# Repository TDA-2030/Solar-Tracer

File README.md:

# 太阳追踪器

## 参考

- https://www.pveducation.org/zh-hans/pvcdrom/%E9%98%B3%E5%85%89%E7%9A%84%E5%B1%9E%E6%80%A7/%E5%A4%AA%E9%98%B3%E7%9A%84%E9%AB%98%E7%B2%BE%E5%BA%A6%E5%AE%9A%E4%BD%8D
- http://106.37.81.211:8082/images/sjsimages/pdf/xw/xwB215_hebing/Y2177876.pdf
- https://jonacappelle.github.io/Master-Thesis/_madgwick_a_h_r_s_8c.html
- https://gml.noaa.gov/grad/solcalc/
- https://zh.planetcalc.com/318/

## 编译

esp-idf 版本：8497af9b77

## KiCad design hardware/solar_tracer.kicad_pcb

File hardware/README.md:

# Ferris Wheel

```
 ________                          __                 __       __ __                         __ 
|        \                        |  \               |  \  _  |  |  \                       |  \
| $$$$$$$______   ______   ______  \$$ _______       | $$ / \ | $| $$____   ______   ______ | $$
| $$__  /      \ /      \ /      \|  \/       \      | $$/  $\| $| $$    \ /      \ /      \| $$
| $$  \|  $$$$$$|  $$$$$$|  $$$$$$| $|  $$$$$$$      | $$  $$$\ $| $$$$$$$|  $$$$$$|  $$$$$$| $$
| $$$$$| $$    $| $$   \$| $$   \$| $$\$$    \       | $$ $$\$$\$| $$  | $| $$    $| $$    $| $$
| $$   | $$$$$$$| $$     | $$     | $$_\$$$$$$\      | $$$$  \$$$| $$  | $| $$$$$$$| $$$$$$$| $$
| $$    \$$     | $$     | $$     | $|       $$      | $$$    \$$| $$  | $$\$$     \\$$     | $$
 \$$     \$$$$$$$\$$      \$$      \$$\$$$$$$$        \$$      \$$\$$   \$$ \$$$$$$$ \$$$$$$$\$$
                                                                                                         
```

~ 一座点缀着繁星般灯光的旋转梦想摩天轮。🌟🎡 ~

## 使用说明

1. 插入电源，等待亮灯，在联网和不联网状态下都会在几秒后进入灯效循环播放，直到收到新的灯效指令。
2. 根据灯的颜色指示，判断当前状态
   1. 亮**红色**说明没有未配置网络，需要按照 `步骤 3` 进行配置
   2. 亮**紫色**说明已经配网，正在连接，只需等待连接完成变成**淡蓝色**即可

3. 配网步骤：
   1. 打开 RainMaker APP 
   2. 点击`添加设备`按钮
   3. 扫描下面的二维码   
   
4. 选择想要连接的 WiFi
5. 输入对应 WiFi 的密码
6. 点击`开始`按钮

## 硬件说明

- 供电输入：12V - 2A
- LED 灯数量：208 * 2
- 摩天轮坐舱数量：16
- 模型比例：1:100

## 灯颜色指示
1. 亮红色：未配网，等待配网
2. 亮紫色：正在联网
3. 亮蓝色：已联网，等待连接云端
4. 亮淡蓝色：已连接云端，可正常使用

## 重置设备方法

当你需要换一个 WiFi 连接或者不要联网的时候需要重置设备。

方法：插上电源等待亮灯一秒后拔掉电源，熄灭后再次插上电源，再次等待亮灯一秒后拔掉电源，如此**反复5次**后插上电源不再拔掉等待灯变成红色即重置成功。

## 编译固件的说明

下载 [ESP-IDF](https://github.com/espressif/esp-idf)，并安装好 ESP-IDF

> 库版本说明：
>
> esp-rainmaker: 7d506420d320a137bce6aaeb69a2059cc162efac
> esp-idf: 97bf63addecd1857a7017a29823a6c70fec99b04

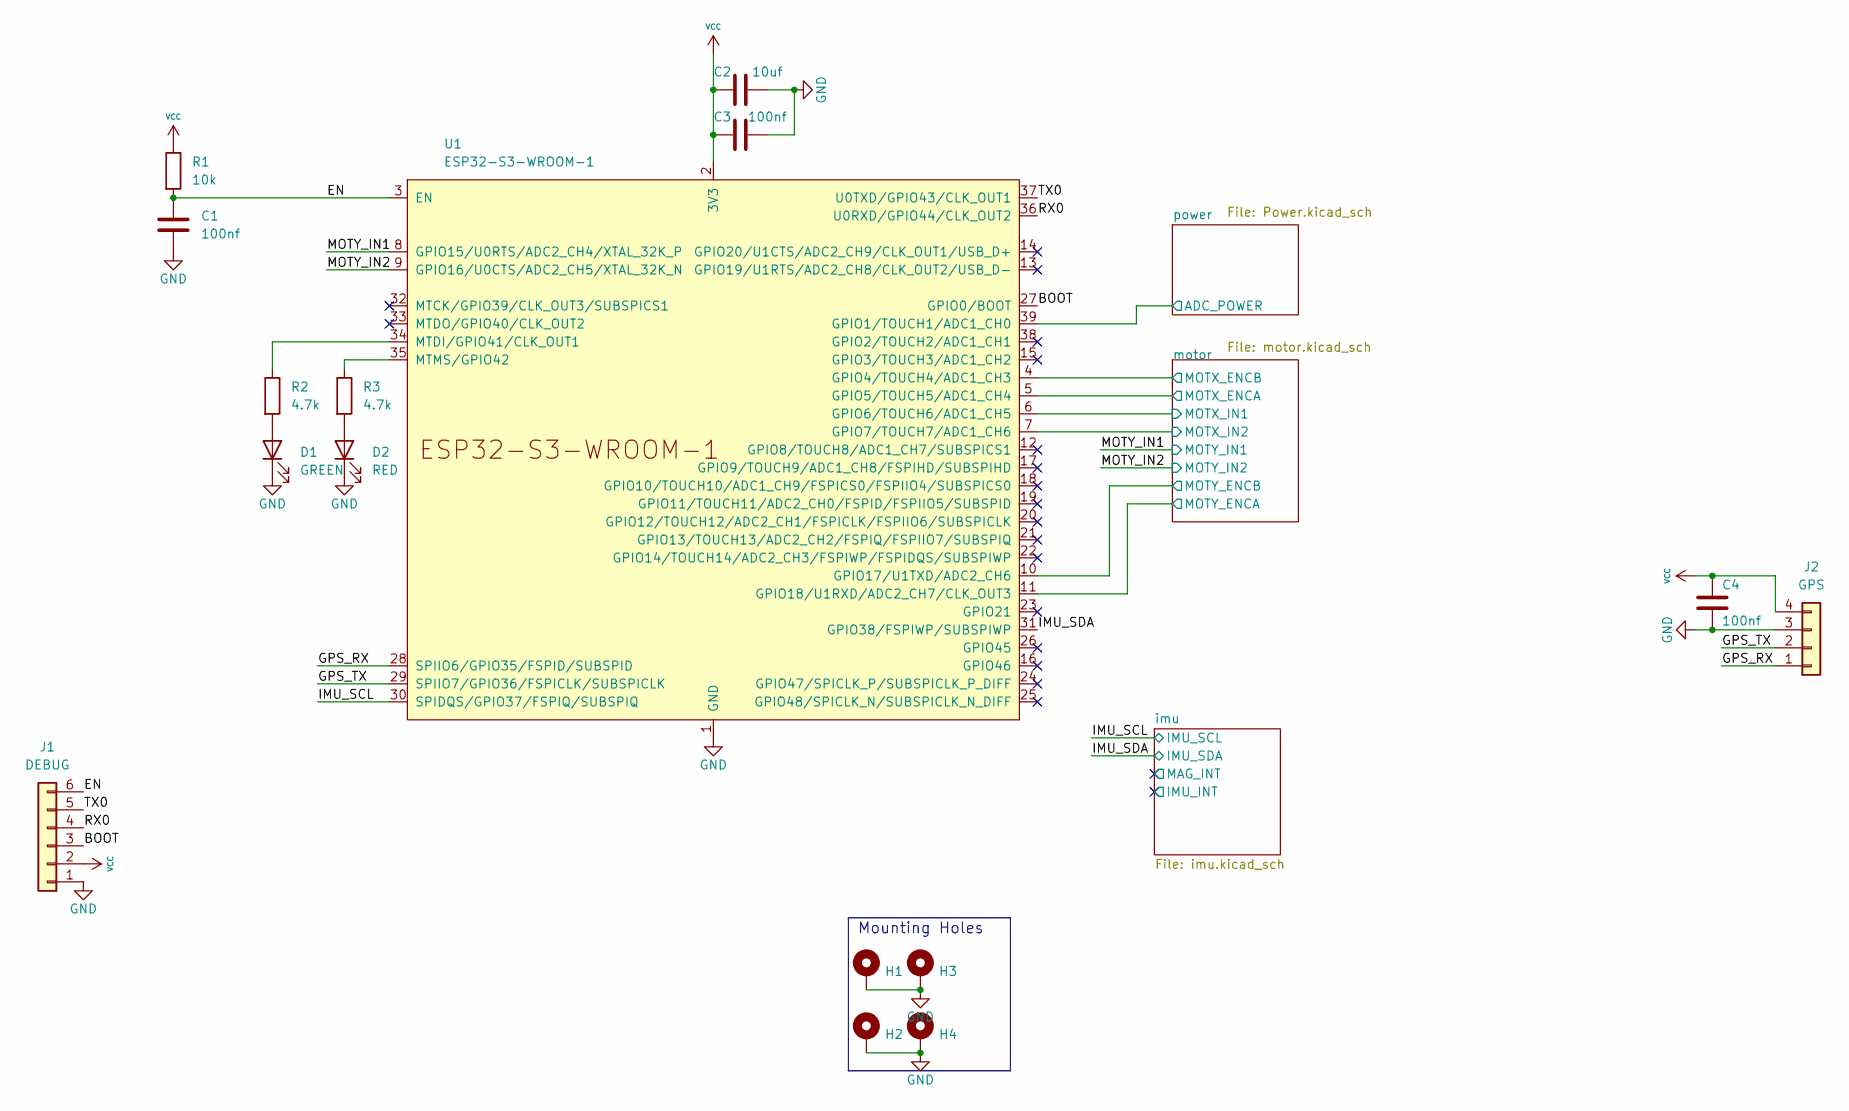
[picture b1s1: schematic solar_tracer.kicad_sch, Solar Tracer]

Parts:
C1, C3, C4: 100nf; C_0402_1005Metric
C2: 10uf; C_0603_1608Metric
D1: GREEN; LED_0603_1608Metric
D2: RED; LED_0603_1608Metric
H1, H2, H3, H4: MountingHole_Pad; MountingHole_3.2mm_M3_Pad_Via
J1: DEBUG; PinHeader_1x06_P2.54mm_Vertical
J2: GPS; PinHeader_1x04_P2.54mm_Vertical
R1: 10k; R_0402_1005Metric
R2, R3: 4.7k; R_0402_1005Metric
U1: ESP32-S3-WROOM-1

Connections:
/BOOT: J1.3, U1.27 (GPIO0/BOOT)
/EN: C1.1, J1.6, R1.2, U1.3 (EN)
/GPS_RX: J2.1, U1.28 (SPIIO6/GPIO35/FSPID/SUBSPID)
/GPS_TX: J2.2, U1.29 (SPIIO7/GPIO36/FSPICLK/SUBSPICLK)
/IMU_SCL: U1.30 (SPIDQS/GPIO37/FSPIQ/SUBSPIQ); also elsewhere on the board
/IMU_SDA: U1.31 (GPIO38/FSPIWP/SUBSPIWP); also elsewhere on the board
/MOTY_IN1: U1.8 (GPIO15/U0RTS/ADC2_CH4/XTAL_32K_P); also elsewhere on the board
/MOTY_IN2: U1.9 (GPIO16/U0CTS/ADC2_CH5/XTAL_32K_N); also elsewhere on the board
/RX0: J1.4, U1.36 (U0RXD/GPIO44/CLK_OUT2)
/TX0: J1.5, U1.37 (U0TXD/GPIO43/CLK_OUT1)
/motor/MOTX_ENCA: U1.5 (GPIO5/TOUCH5/ADC1_CH4); also elsewhere on the board
/motor/MOTX_ENCB: U1.4 (GPIO4/TOUCH4/ADC1_CH3); also elsewhere on the board
/motor/MOTX_IN1: U1.6 (GPIO6/TOUCH6/ADC1_CH5); also elsewhere on the board
/motor/MOTX_IN2: U1.7 (GPIO7/TOUCH7/ADC1_CH6); also elsewhere on the board
/motor/MOTY_ENCA: U1.11 (GPIO18/U1RXD/ADC2_CH7/CLK_OUT3); also elsewhere on the board
/motor/MOTY_ENCB: U1.10 (GPIO17/U1TXD/ADC2_CH6); also elsewhere on the board
/power/ADC_POWER: U1.39 (GPIO1/TOUCH1/ADC1_CH0); also elsewhere on the board
GND: C1.2, C2.2, C3.2, C4.2, D1.1 (K), D2.1 (K), H1.1, H2.1, H3.1, H4.1, J1.1, J2.3, U1.1 (GND), U1.40 (GND), U1.41 (GND); also elsewhere on the board
unnamed: D1.2 (A), R2.2
unnamed: D2.2 (A), R3.2
unnamed: R2.1, U1.34 (MTDI/GPIO41/CLK_OUT1)
unnamed: R3.1, U1.35 (MTMS/GPIO42)
VCC: C2.1, C3.1, C4.1, J1.2, J2.4, R1.1, U1.2 (3V3); also elsewhere on the board

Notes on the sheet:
Mounting Holes

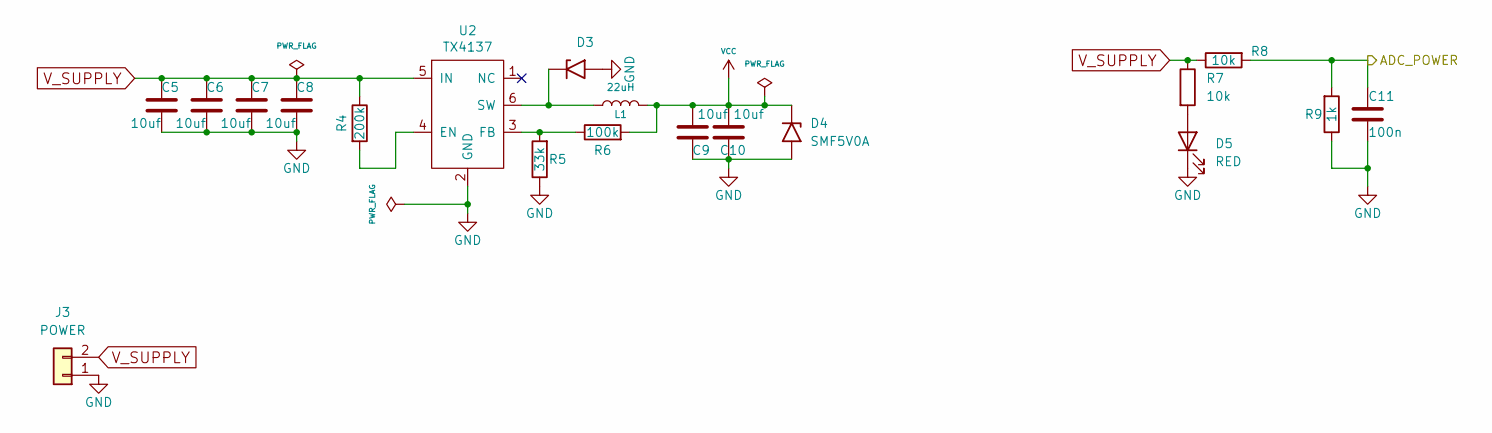
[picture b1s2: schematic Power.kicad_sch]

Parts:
C5, C6, C7, C8: 10uf; C_1206_3216Metric
C9, C10: 10uf; C_0603_1608Metric
C11: 100n; C_0402_1005Metric
D3: B5819W SL; D_SOD-123
D4: SMF5V0A; D_SMF
D5: RED; LED_0603_1608Metric
J3: POWER; PinHeader_1x02_P2.54mm_Vertical
L1: 22uH; L_Taiyo-Yuden_NR-40xx
R4: 200k; R_0402_1005Metric
R5: 33k; R_0402_1005Metric
R6: 100k; R_0402_1005Metric
R7, R8: 10k; R_0402_1005Metric
R9: 1k; R_0402_1005Metric
U2: TX4137; SOT-23-6

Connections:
/power/ADC_POWER: C11.2, R8.2, R9.2; also elsewhere on the board
GND: C5.1, C6.1, C7.1, C8.1, C9.1, C10.1, C11.1, D3.2 (A2), D4.2 (A2), D5.1 (K), J3.1, R5.1, R9.1, U2.2 (GND); also elsewhere on the board
unnamed: D3.1 (A1), L1.1, U2.6 (SW)
unnamed: D5.2 (A), R7.2
unnamed: R4.2, U2.4 (EN)
unnamed: R5.2, R6.1, U2.3 (FB)
VCC: C9.2, C10.2, D4.1 (A1), L1.2, R6.2; also elsewhere on the board
V_SUPPLY: C5.2, C6.2, C7.2, C8.2, J3.2, R4.1, R7.1, R8.1, U2.5 (IN); also elsewhere on the board

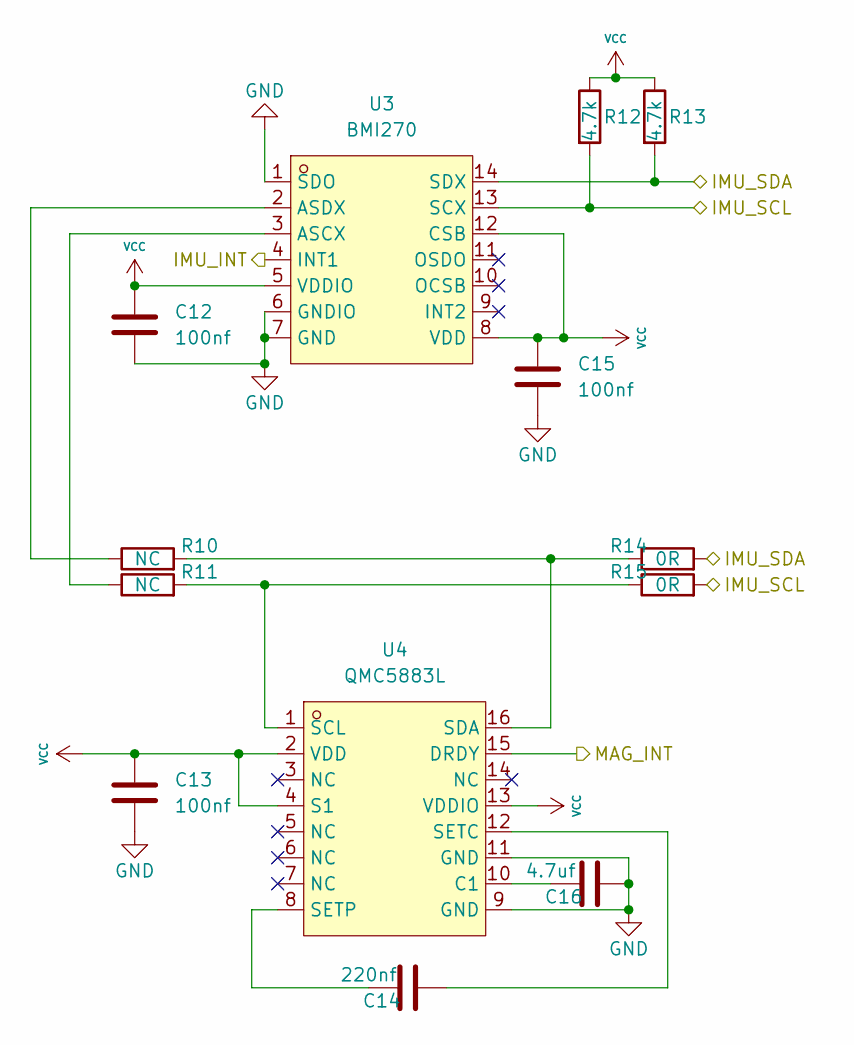
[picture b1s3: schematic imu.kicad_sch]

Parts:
C12, C13, C15: 100nf; C_0402_1005Metric
C14: 220nf; C_0402_1005Metric
C16: 4.7uf; C_0402_1005Metric
R10, R11: NC; R_0402_1005Metric
R12, R13: 4.7k; R_0402_1005Metric
R14, R15: 0R; R_0402_1005Metric
U3: BMI270; LGA-14_L3.0-W2.5-P0.50-BR; LCSC Part C2836813
U4: QMC5883L; LGA-16_L3.0-W3.0-P0.50-BL_SQ; LCSC Part C976032

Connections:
/IMU_SCL: R12.2, R15.2, U3.13 (SCX); also elsewhere on the board
/IMU_SDA: R13.2, R14.2, U3.14 (SDX); also elsewhere on the board
/imu/IMU_INT: U3.4 (INT1)
/imu/MAG_INT: U4.15 (DRDY)
GND: C12.1, C13.1, C15.1, C16.1, U3.1 (SDO), U3.6 (GNDIO), U3.7 (GND), U4.9 (GND), U4.11 (GND); also elsewhere on the board
unnamed: C14.1, U4.12 (SETC)
unnamed: C14.2, U4.8 (SETP)
unnamed: C16.2, U4.10 (C1)
unnamed: R10.1, U3.2 (ASDX)
unnamed: R10.2, R14.1, U4.16 (SDA)
unnamed: R11.1, U3.3 (ASCX)
unnamed: R11.2, R15.1, U4.1 (SCL)
VCC: C12.2, C13.2, C15.2, R12.1, R13.1, U3.5 (VDDIO), U3.8 (VDD), U3.12 (CSB), U4.2 (VDD), U4.4 (S1), U4.13 (VDDIO); also elsewhere on the board

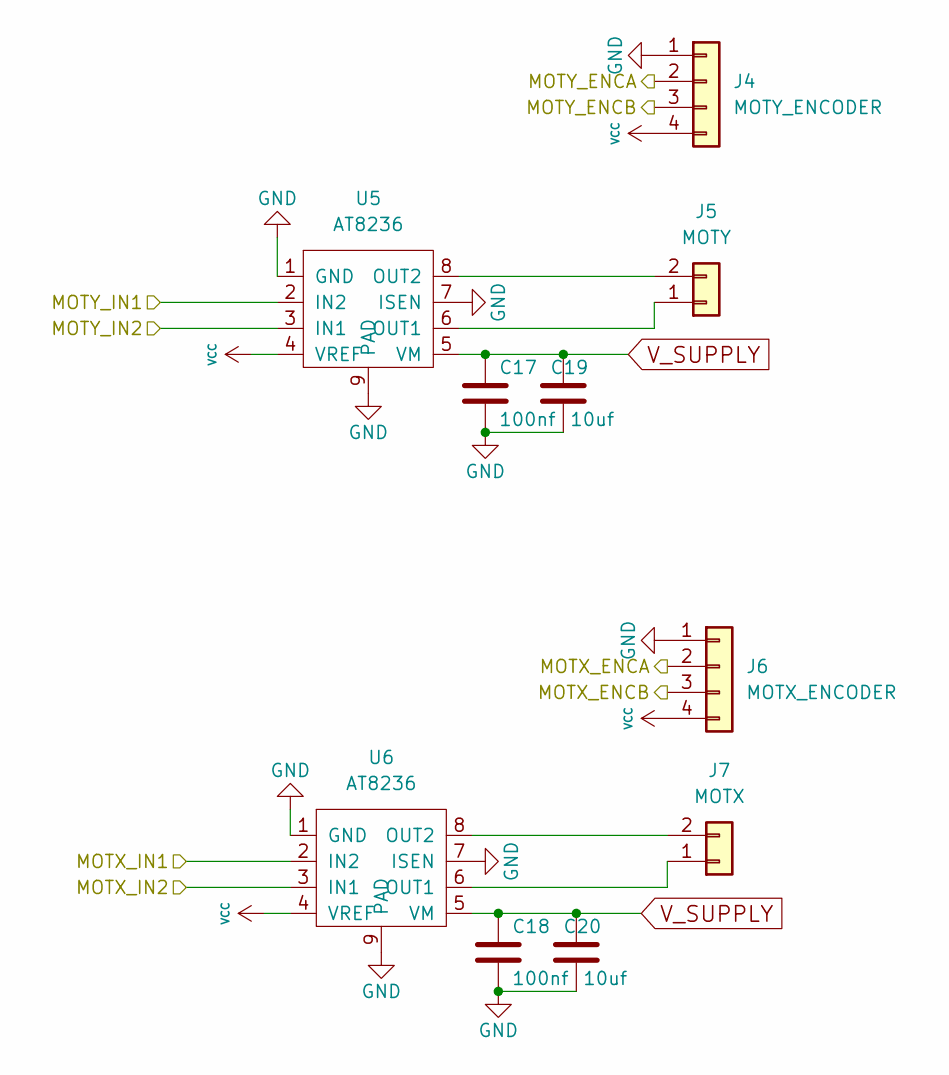
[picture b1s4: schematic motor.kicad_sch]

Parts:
C17, C18: 100nf; C_0402_1005Metric
C19, C20: 10uf; C_0603_1608Metric
J4: MOTY_ENCODER; PinHeader_1x04_P2.54mm_Vertical
J5: MOTY; PinHeader_1x02_P2.54mm_Vertical
J6: MOTX_ENCODER; PinHeader_1x04_P2.54mm_Vertical
J7: MOTX; PinHeader_1x02_P2.54mm_Vertical
U5, U6: AT8236; SOIC-8-1EP_3.9x4.9mm_P1.27mm_EP2.29x3mm

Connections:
/MOTY_IN1: U5.2 (IN2); also elsewhere on the board
/MOTY_IN2: U5.3 (IN1); also elsewhere on the board
/motor/MOTX_ENCA: J6.2; also elsewhere on the board
/motor/MOTX_ENCB: J6.3; also elsewhere on the board
/motor/MOTX_IN1: U6.2 (IN2); also elsewhere on the board
/motor/MOTX_IN2: U6.3 (IN1); also elsewhere on the board
/motor/MOTY_ENCA: J4.2; also elsewhere on the board
/motor/MOTY_ENCB: J4.3; also elsewhere on the board
GND: C17.2, C18.2, C19.1, C20.1, J4.1, J6.1, U5.1 (GND), U5.7 (ISEN), U5.9 (PAD), U6.1 (GND), U6.7 (ISEN), U6.9 (PAD); also elsewhere on the board
unnamed: J5.1, U5.6 (OUT1)
unnamed: J5.2, U5.8 (OUT2)
unnamed: J7.1, U6.6 (OUT1)
unnamed: J7.2, U6.8 (OUT2)
VCC: J4.4, J6.4, U5.4 (VREF), U6.4 (VREF); also elsewhere on the board
V_SUPPLY: C17.1, C18.1, C19.2, C20.2, U5.5 (VM), U6.5 (VM); also elsewhere on the board

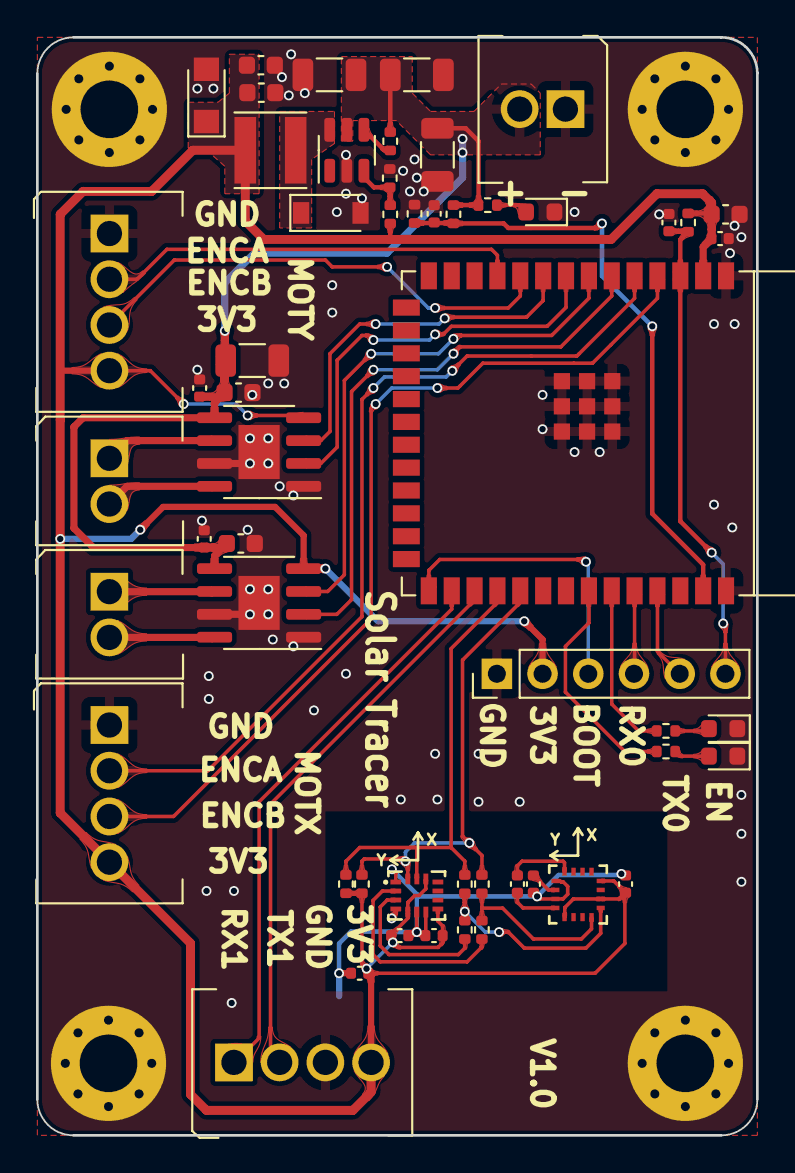
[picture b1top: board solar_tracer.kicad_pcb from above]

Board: 2 copper layers, 40.0 x 61.0 mm, 58 parts (0 on the bottom side), 39 nets.

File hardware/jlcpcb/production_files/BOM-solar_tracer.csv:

Comment,Designator,Footprint,LCSC
BMI270,U3,LGA-14_L3.0-W2.5-P0.50-BR,C2836813
QMC5883L,U4,LGA-16_L3.0-W3.0-P0.50-BL_SQ,C976032
MountingHole_Pad,H4,MountingHole_3.2mm_M3_Pad_Via,
MountingHole_Pad,H1,MountingHole_3.2mm_M3_Pad_Via,
10uf,C10,C_0603,
10uf,C9,C_0603,
10uf,C7,C_1206_3216Metric,
10uf,C2,C_0603,
AT8236,U6,SOIC-8-1EP_3.9x4.9mm_P1.27mm_EP2.29x3mm,
AT8236,U5,SOIC-8-1EP_3.9x4.9mm_P1.27mm_EP2.29x3mm,
TX4137,U2,SOT-23-6,
ESP32-S3-WROOM-1,U1,ESP32-S3-WROOM-1,
0R,R15,R_0402,
0R,R14,R_0402,
4.7k,R13,R_0402,
4.7k,R12,R_0402,
NC,R11,R_0402,
NC,R10,R_0402,
1k,R9,R_0402,
10k,R8,R_0402,
10k,R7,R_0402,
100k,R6,R_0402,
33k,R5,R_0402,
200k,R4,R_0402,
4.7k,R3,R_0402,
4.7k,R2,R_0402,
10k,R1,R_0402,
22uH,L1,L_Taiyo-Yuden_NR-40xx,
MOTX,J7,PinHeader_1x02_P2.54mm_Vertical,
MOTX_ENCODER,J6,PinHeader_1x04_P2.54mm_Vertical,
MOTY,J5,PinHeader_1x02_P2.54mm_Vertical,
MOTY_ENCODER,J4,PinHeader_1x04_P2.54mm_Vertical,
POWER,J3,PinHeader_1x02_P2.54mm_Vertical,
GPS,J2,PinHeader_1x04_P2.54mm_Vertical,
DEBUG,J1,PinHeader_1x06_P2.54mm_Vertical,
MountingHole_Pad,H3,MountingHole_3.2mm_M3_Pad_Via,
MountingHole_Pad,H2,MountingHole_3.2mm_M3_Pad_Via,
RED,D5,LED_0603,
SMF5V0A,D4,D_SMF,
B5819W SL,D3,D_SOD-123,
RED,D2,LED_0603,
GREEN,D1,LED_0603,
10uf,C20,C_0603,
10uf,C19,C_0603,
100nf,C18,C_0402,
100nf,C17,C_0402,
4.7uf,C16,C_0402,
100nf,C15,C_0402,
220nf,C14,C_0402,
100nf,C13,C_0402,
100nf,C12,C_0402,
100n,C11,C_0402,
10uf,C8,C_1206_3216Metric,
10uf,C6,C_1206_3216Metric,
10uf,C5,C_1206_3216Metric,
100nf,C4,C_0402,
100nf,C3,C_0402,
100nf,C1,C_0402,

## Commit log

2025-03-02 hw: add library
2025-03-02 fw: update
2025-03-03 fw: add web server
2025-03-04 fw: update webserver
2025-03-05 fw: update front to vue3+vite
2025-03-06 fw: add setting json for web server
2025-03-06 front: add pid parameter card
2025-03-10 fw: temp
2025-03-16 fw: add bmi270 and remove wit imu
2025-03-27 fw: update for motor
2025-03-28 fw : updte
2025-03-31 fw: refactor motor
2025-03-31 hw: update
2025-04-01 web front: update
2025-04-07 add 3d
2025-06-02 update web
2025-06-02 update for new shell
2025-06-02 add ota web
2025-06-08 update for new data fusion
2025-06-10 3d: update
